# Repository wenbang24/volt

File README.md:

# Volt
A portable guitar amp that works with your bluetooth device, so you can play anywhere, anytime.

## BOM
|Designator    |Footprint         |Quantity|Value       |LCSC Part #| Link |
|--------------|------------------|--------|------------|-----------|------|
|C1, C13       |0402              |2       |1u          |C14445     |[LCSC](https://lcsc.com/product-detail/Multilayer-Ceramic-Capacitors-MLCC-SMD-SMT_Samsung-Electro-Mechanics-CL05A105KP5NNNC_C14445.html?s_z=n_C14445)|
|C10, C3, C5   |0402              |3       |100n        |C1525      |[LCSC](https://lcsc.com/product-detail/Multilayer-Ceramic-Capacitors-MLCC-SMD-SMT_Samsung-Electro-Mechanics-CL05B104KO5NNNC_C1525.html?s_z=n_C1525)|
|C2, C8        |0402              |2       |4u7         |C23733     |[LCSC](https://lcsc.com/product-detail/Multilayer-Ceramic-Capacitors-MLCC-SMD-SMT_Samsung-Electro-Mechanics-CL05A475MP5NRNC_C23733.html?s_z=n_C23733)|
|C4, C6        |0805              |2       |47u         |C1954938   |[LCSC](https://lcsc.com/product-detail/Tantalum-Capacitors_Kyocera-AVX-TLJR476M010R3200_C1954938.html?s_z=n_C1954938)|
|C7            |1206              |1       |100u        |C883598    |[LCSC](https://lcsc.com/product-detail/Multilayer-Ceramic-Capacitors-MLCC-SMD-SMT_Murata-Electronics-GRM31CR61A107MEA8L_C883598.html?s_z=n_C883598)|
|C9            |0402              |1       |0.22u       |C16772     |[LCSC](https://lcsc.com/product-detail/Multilayer-Ceramic-Capacitors-MLCC-SMD-SMT_Samsung-Electro-Mechanics-CL05B224KO5NNNC_C16772.html?s_z=n_C16772)|
|R1            |0402              |1       |1k          |C26083     |[LCSC](https://lcsc.com/product-detail/Chip-Resistor-Surface-Mount_UNI-ROYAL-Uniroyal-Elec-0402WGF1004TCE_C26083.html?s_z=n_C26083)|
|R10, R3       |0402              |2       |4k7         |C25900     |[LCSC](https://lcsc.com/product-detail/Chip-Resistor-Surface-Mount_UNI-ROYAL-Uniroyal-Elec-0402WGF4701TCE_C25900.html?s_z=n_C25900)|
|R11, R4, R6   |0402              |3       |10k         |C25744     |[LCSC](https://lcsc.com/product-detail/Chip-Resistor-Surface-Mount_UNI-ROYAL-Uniroyal-Elec-0402WGF1002TCE_C25744.html?s_z=n_C25744)|
|R2, R7, R8, R9|0402              |4       |100k        |C25741     |[LCSC](https://lcsc.com/product-detail/Chip-Resistor-Surface-Mount_UNI-ROYAL-Uniroyal-Elec-0402WGF1003TCE_C25741.html?s_z=n_C25741)|
|R5            |0402              |1       |220k        |C25767     |[LCSC](https://lcsc.com/product-detail/Chip-Resistor-Surface-Mount_UNI-ROYAL-Uniroyal-Elec-0402WGF2203TCE_C25767.html?s_z=n_C25767)|
|SW1           |SW_SPDT_PCM12     |1       |SW_SPDT     |C221841    |[LCSC](https://lcsc.com/product-detail/Slide-Switches_C-K-PCM12SMTR_C221841.html?s_z=n_C221841)|
|U3            |VREG_LM7805MP_NOPB|1       |LM7805_TO220|C2848241   |[LCSC](https://lcsc.com/product-detail/Voltage-Regulators-Linear-Low-Drop-Out-LDO-Regulators_Texas-Instruments-LM7805MPX-NOPB_C2848241.html?s_z=n_C2848241)|

Price: $6.47
### Parts to source yourself
|Designator    |Footprint         |Quantity|Value       | Link |
|--------------|------------------|--------|------------|------|
|U1|DIP-8|1|TL072|[AliExpress](https://www.aliexpress.com/item/1005006135219871.html?spm=a2g0o.order_list.order_list_main.17.5d4e1802HO5hMP)|
|U2||1|BT 5.3 Audio Transmitter|[AliExpress](https://www.aliexpress.com/item/1005006761214266.html?spm=a2g0o.order_list.order_list_main.35.5d4e1802HO5hMP)|
|J1||1|1/4" Audio Jack|[AliExpress](https://www.aliexpress.com/item/1005006199010497.html?pdp_ext_f=%7B%22sku_id%22%3A%2212000036235541089%22%7D&sourceType=1&spm=a2g0o.wish-manage-home.0.0)|
|J2||1|9V Battery Connector|[AliExpress](https://www.aliexpress.com/item/1005003688602261.html?spm=a2g0o.order_list.order_list_main.23.531a1802qO4r9D)|
|RV1||1|100k Potentiometer (logarithmic)|[Core Electronics](https://core-electronics.com.au/rotary-potentiometer-100k-ohm-logarithmic-panel-mount.html)|
|RV2||1|100k Potentiometer (linear)|[Core Electronics](https://core-electronics.com.au/rotary-potentiometer-100k-ohm-linear-panel-mount.html)|
|||4|M2 Screws|[AliExpress](https://www.aliexpress.com/item/4000970993800.html?spm=a2g0o.productlist.main.1.58de4aHV4aHVjt&algo_pvid=0fc23f4e-c433-440c-a35c-41e9ab94c65d&algo_exp_id=0fc23f4e-c433-440c-a35c-41e9ab94c65d-0&pdp_ext_f=%7B%22order%22%3A%222927%22%2C%22eval%22%3A%221%22%7D&pdp_npi=4%40dis%21AUD%211.84%211.68%21%21%211.19%211.09%21%402103244617511662003371305ef768%2110000013100721958%21sea%21AU%212685707787%21X&curPageLogUid=a6nSASSgxzOP&utparam-url=scene%3Asearch%7Cquery_from%3A)|

Price: $16.57

Also:
- 9V Battery
- Case (files in `case/`)
- Some wires & solder

Total PCB & PCBA Price: $32.51

Total Price: $49.08

**Total Price + est. shipping**: $60.00

(prices converted from AUD to USD, accurate as of 2025-06-29)

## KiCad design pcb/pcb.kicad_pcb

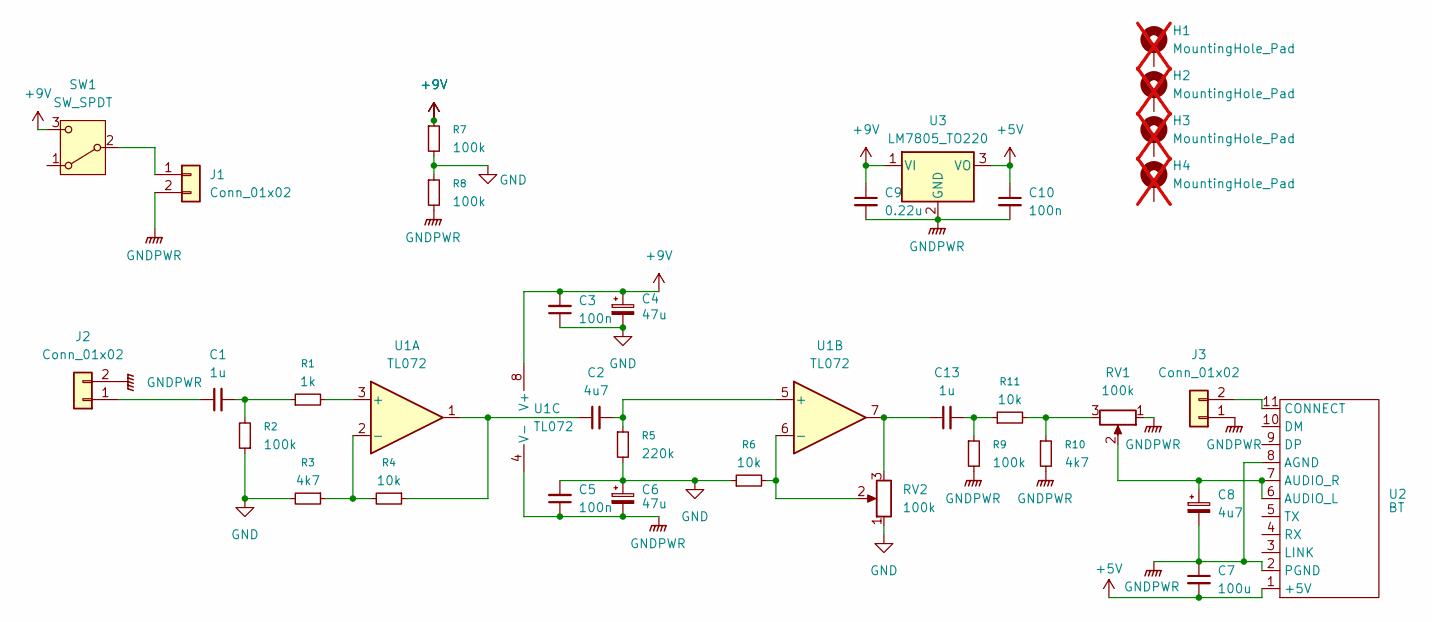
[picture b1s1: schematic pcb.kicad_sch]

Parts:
C1, C13: 1u; C_0402_1005Metric; LCSC C14445
C2, C8: 4u7; C_0402_1005Metric; LCSC C23733
C3, C5, C10: 100n; C_0402_1005Metric; LCSC C1525
C4, C6: 47u; C_0805_2012Metric; LCSC C1954938
C7: 100u; C_1206_3216Metric; LCSC C883598
C9: 0.22u; C_0402_1005Metric; LCSC C16772
H1, H2, H3, H4: MountingHole_Pad; MountingHole_2.2mm_M2; not fitted
J1, J2, J3: Conn_01x02; PinHeader_1x02_P2.54mm_Vertical
R1: 1k; R_0402_1005Metric; LCSC C26083
R2, R7, R8, R9: 100k; R_0402_1005Metric; LCSC C25741
R3, R10: 4k7; R_0402_1005Metric; LCSC C25900
R4, R6, R11: 10k; R_0402_1005Metric; LCSC C25744
R5: 220k; R_0402_1005Metric; LCSC C25767
RV1, RV2: 100k; PinHeader_1x03_P2.54mm_Vertical
SW1: SW_SPDT; SW_SPDT_PCM12; LCSC C221841
U1: TL072; DIP254P762X533-8
U2: BT; BT_Transmitter
U3: LM7805_TO220; VREG_LM7805MP_NOPB; LCSC C2848241

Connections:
+5V: C7.2, C10.1, U2.1 (+5V), U3.3 (VO)
+9V: C3.2, C4.1, C9.1, R7.1, SW1.3 (C), U1.8 (V+), U3.1 (VI)
GND: C3.1, C4.2, C5.2, C6.1, R2.1, R3.2, R5.2, R6.1, R7.2, R8.1, RV2.1
GNDPWR: C5.1, C6.2, C7.1, C8.2, C9.2, C10.2, J1.2, J2.2, J3.1, R8.2, R9.2, R10.2, RV1.1, U1.4 (V-), U2.2 (PGND), U2.8 (AGND), U3.2 (GND)
unnamed: C1.2, R1.1, R2.2
unnamed: C2.1, R4.1, U1.1
unnamed: C13.1, RV2.3, U1.7
unnamed: C13.2, R9.1, R11.1
unnamed: J1.1, SW1.2 (B)
unnamed: C1.1, J2.1
unnamed: J3.2, U2.11 (CONNECT)
unnamed: R10.1, R11.2, RV1.3
unnamed: R1.2, U1.3 (+)
unnamed: R3.1, R4.2, U1.2 (-)
unnamed: C2.2, R5.1, U1.5 (+)
unnamed: R6.2, RV2.2, U1.6 (-)
unnamed: C8.1, RV1.2, U2.6 (AUDIO_L), U2.7 (AUDIO_R)

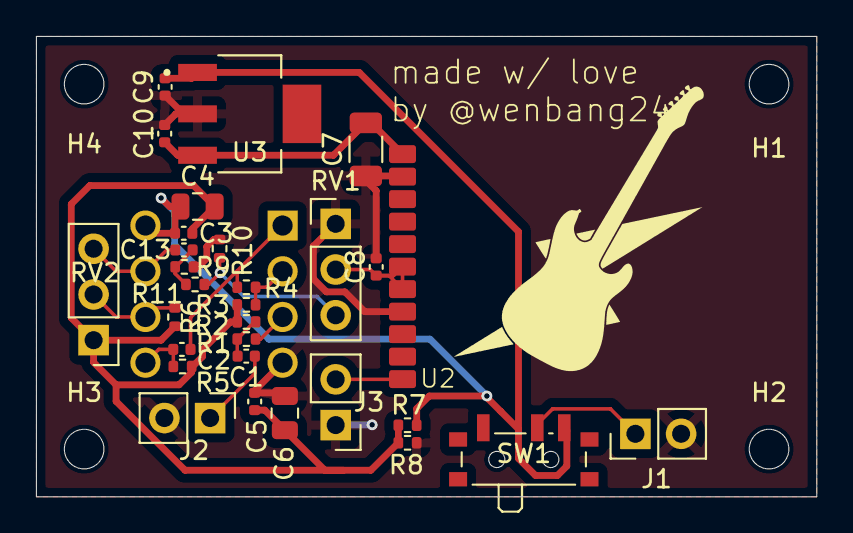
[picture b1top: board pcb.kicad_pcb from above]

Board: 2 copper layers, 43.4 x 25.6 mm, 35 parts (1 on the bottom side), 17 nets.

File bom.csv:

Designator,Footprint,Quantity,Value,LCSC Part #,Link
"C1, C13",0402,2,1u,C14445,https://lcsc.com/product-detail/Multilayer-Ceramic-Capacitor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
"C10, C3, C5",0402,3,100n,C1525,https://lcsc.com/product-detail/Multilayer-Ceramic-Capacitor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
"C2, C8",0402,2,4u7,C23733,https://lcsc.com/product-detail/Multilayer-Ceramic-Capacitor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
"C4, C6",0805,2,47u,C1954938,https://lcsc.com/product-detail/Tantalum-Capacitors_Kyocera-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
C7,1206,1,100u,C883598,https://lcsc.com/product-detail/Multilayer-Ceramic-Capacitor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
C9,0402,1,0.22u,C16772,https://lcsc.com/product-detail/Multilayer-Ceramic-Capacitor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
R1,0402,1,1k,C26083,https://lcsc.com/product-detail/Chip-Resistor-Surface-Mount_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
"R10, R3",0402,2,4k7,C25900,https://lcsc.com/product-detail/Chip-Resistor-Surface-Mount_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
"R11, R4, R6",0402,3,10k,C25744,https://lcsc.com/product-detail/Chip-Resistor-Surface-Mount_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
"R2, R7, R8, R9",0402,4,100k,C25741,https://lcsc.com/product-detail/Chip-Resistor-Surface-Mount_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
R5,0402,1,220k,C25767,https://lcsc.com/product-detail/Chip-Resistor-Surface-Mount_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
SW1,SW_SPDT_PCM12,1,SW_SPDT,C221841,https://lcsc.com/product-detail/Slide-Switches_C-K-PCM12SMTR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
U3,VREG_LM7805MP_NOPB,1,LM7805_TO220,C2848241,https://lcsc.com/product-detail/Voltage-Regulators-Linear-Lo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
U1,DIP-8,1,TL072,,https://www.aliexpress.com/item/1005006135219871.html?spm=a2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
U2,,1,BT 5.3 Audio Transmitter,,https://www.aliexpress.com/item/1005006761214266.html?spm=a2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
J1,,1,"1/4"" Audio Jack",,https://www.aliexpress.com/item/1005006199010497.html?pdp_ex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
J2,,1,9V Battery Connector,,https://www.aliexpress.com/item/1005003688602261.html?spm=a2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
RV1,,1,100k Potentiometer (logarithmic),,https://core-electronics.com.au/rotary-potentiometer-100k-oh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
RV2,,1,100k Potentiometer (linear),,https://core-electronics.com.au/rotary-potentiometer-100k-oh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
,,4,M2 Screw,,https://www.aliexpress.com/item/4000970993800.html?spm=a2g0o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

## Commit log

2025-06-18 pcb initial commit
2025-06-18 journal and readme
2025-06-18 journal entry
2025-06-20 journal
2025-06-20 fix pin orientation in symbols
2025-06-21 schematic v1
2025-06-21 [ImgBot] Optimize images
    *Total -- 354.36kb -> 105.37kb (70.26%)
    /img/schematicv1.png -- 201.20kb -> 52.41kb (73.95%)
    /img/u1.png -- 105.86kb -> 34.79kb (67.14%)
    /img/u2.png -- 47.29kb -> 18.18kb (61.56%)
2025-06-21 small stylistic changes to schematic
2025-06-22 footprints, a bit of pcb
2025-06-22 pcb v1
2025-06-23 pcb v2: distortion stage
2025-06-23 schematic v2, spicing
2025-06-23 gitignore
2025-06-23 simulations
2025-06-24 fix mistake in input
2025-06-24 voltage cap
2025-06-24 schematic v3
2025-06-28 pcb v2
2025-06-28 [ImgBot] Optimize images
    *Total -- 12,836.88kb -> 5,361.24kb (58.24%)
    /img/schematicv3.1.png -- 245.01kb -> 63.80kb (73.96%)
    /img/schematicv3.2.png -- 248.29kb -> 65.83kb (73.49%)
    /img/schematicv3.png -- 213.52kb -> 58.49kb (72.61%)
    /img/schematicv2.png -- 219.17kb -> 61.16kb (72.1%)
    /img/sim2_2.png -- 1,557.36kb -> 632.07kb (59.41%)
2025-06-29 case & render
2025-06-29 change caps, do bom, reroute, readme, ship, etc
2025-06-29 total time
2025-06-29 made logo
2025-06-29 logo & silkscreen art
2025-06-29 add pcb to readme
2025-06-29 more images
2025-06-30 on switch hole in case
2025-07-02 update bom to table form and include links
2025-07-03 connect button footprint
2025-07-15 built it
2025-07-15 [ImgBot] Optimize images
    *Total -- 17,198.51kb -> 14,125.04kb (17.87%)
    /img/logo.png -- 79.68kb -> 29.84kb (62.55%)
    /img/pcbv2.2_1.png -- 199.64kb -> 95.62kb (52.11%)
    /img/pcbv2.1.png -- 540.17kb -> 278.14kb (48.51%)
    /img/casev1.png -- 242.88kb -> 127.31kb (47.58%)
    /img/pcbv2.2_3.png -- 450.50kb -> 238.60kb (47.04%)
